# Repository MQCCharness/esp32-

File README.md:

# ESP32-S3 MOC 2.0 开发板资料库

HELLO STEM/嘉年创奇 **ESP32-S3 MOC 2.0** 开发板（生产商：惠州市百育科技有限公司，执行标准 Q/BYKJ 001-2023）的逆向调研、出厂备份与恢复工具合集。

## 板卡档案

| 项目 | 内容 |
|------|------|
| 主控 | ESP32-S3，QFN56，revision v0.2（乐鑫） |
| 内核 | 双核 Xtensa LX7 @ 240 MHz |
| 无线 | Wi-Fi + 蓝牙 5 (LE) |
| 片内 PSRAM | 8 MB（封装内嵌入式，AP 厂商） |
| 板载 Flash | 16 MB，四线 SPI |
| USB | 芯片内置 USB-Serial/JTAG（无外置串口桥），Windows 免驱 |
| 出厂固件 | Arduino 框架测试程序（esp-idf v4.4.4，2023-02-08 编译） |
| 出厂分区 | Arduino OTA 布局：app0/app1 各 1.25MB + SPIFFS 1.375MB |

实测芯片 MAC：`14:c1:9f:46:78:4c`

## 目录说明

```
├── factory_backup/          出厂 Flash 完整备份（4MB 镜像 + 校验与档案说明）
├── one_click_restore/       一键恢复包（免安装，拷到 U 盘即可在任意 Windows 电脑使用）
│   ├── 一键恢复.bat          双击即可恢复出厂（自动识别 COM 口）
│   ├── esptool.exe          乐鑫官方烧录工具独立版 v5.3.1
│   ├── factory_full_4M.bin  出厂固件镜像
│   └── 使用说明.txt
├── caixukun_ascii/          串口 ASCII 动画项目（MicroPython，视频转字符画循环播放）
│   ├── main.py              板端播放器（开机自动播放，REPL Ctrl-C 打断）
│   ├── viewer.py            电脑端串口播放器（自动找 COM 口）
│   ├── 启动动画.bat          双击看动画
│   └── convert_to_ascii.py  视频 → ASCII 帧包转换器（本地使用）
├── third_party/esp32-edu/   韩国教育机构配套课程（git subtree 合并，含板子标注实拍图）
└── docs/                    板卡引脚表、调研结论、踩坑记录与操作规范
```

> **第三方来源声明**：`third_party/esp32-edu` 来自 [parkdongbae-afk/esp32-edu](https://github.com/parkdongbae-afk/esp32-edu)（韩国中学 ESP32-S3-MOC 教学项目，git subtree 合并，版权归原作者；该仓库未见 LICENSE 文件，仅作学习研究用途引用）。

## 快速上手

- **看动画**：双击 `caixukun_ascii/启动动画.bat`（需先 USB 连板）
- **恢复出厂**：双击 `one_click_restore/一键恢复.bat`
- **踩坑速查**：[docs/踩坑记录与操作规范.md](docs/踩坑记录与操作规范.md)（CDC 挂死、UART 重建限制、串口丢包等 7 个坑的根因与 SOP）

## 一键恢复出厂

1. USB 连接开发板
2. 双击 `one_click_restore/一键恢复.bat`
3. 等待约 20 秒，看到「★ 恢复成功」即可

或手动执行：

```bash
esptool.exe --port COMx --baud 921600 write-flash 0x0 factory_full_4M.bin
```

## 引脚速查

详见 [docs/ESP32-S3-MOC-套件引脚表.md](docs/ESP32-S3-MOC-套件引脚表.md)。常用：DHT11→GPIO4，超声波→GPIO5/18，OLED→GPIO8/9，舵机→GPIO14，蜂鸣器→GPIO12，NeoPixel→GPIO13。

**硬约束**：GPIO19/20=USB，GPIO26-32=Flash，GPIO35-37 因 8MB PSRAM 不可用，GPIO0/3/45/46 为 strapping 脚。

## 调研结论（2026-08）

- 该厂商无公开的原理图/引脚图/恢复镜像，公网无索引
- 同型号板卡用于韩国中学编程教育：配套课程软件 [esp32-edu](https://github.com/parkdongbae-afk/esp32-edu)，其数据文件给出了套件标准接线（已整理为上方引脚表）
- ESP32-S3 的 ROM 下载模式无法被软件破坏，**这块板软件层面刷不死**，任何情况下都可用 esptool 重刷

## 备份完整性

`factory_full_4M.bin` SHA256：`ac49514050ef4841609e4c4b86767b0878150f8ae4bd8d039c1a32f8657c1f6b`（4,194,304 字节；4MB 之后至 16MB 为出厂空白 0xFF，已抽样验证）

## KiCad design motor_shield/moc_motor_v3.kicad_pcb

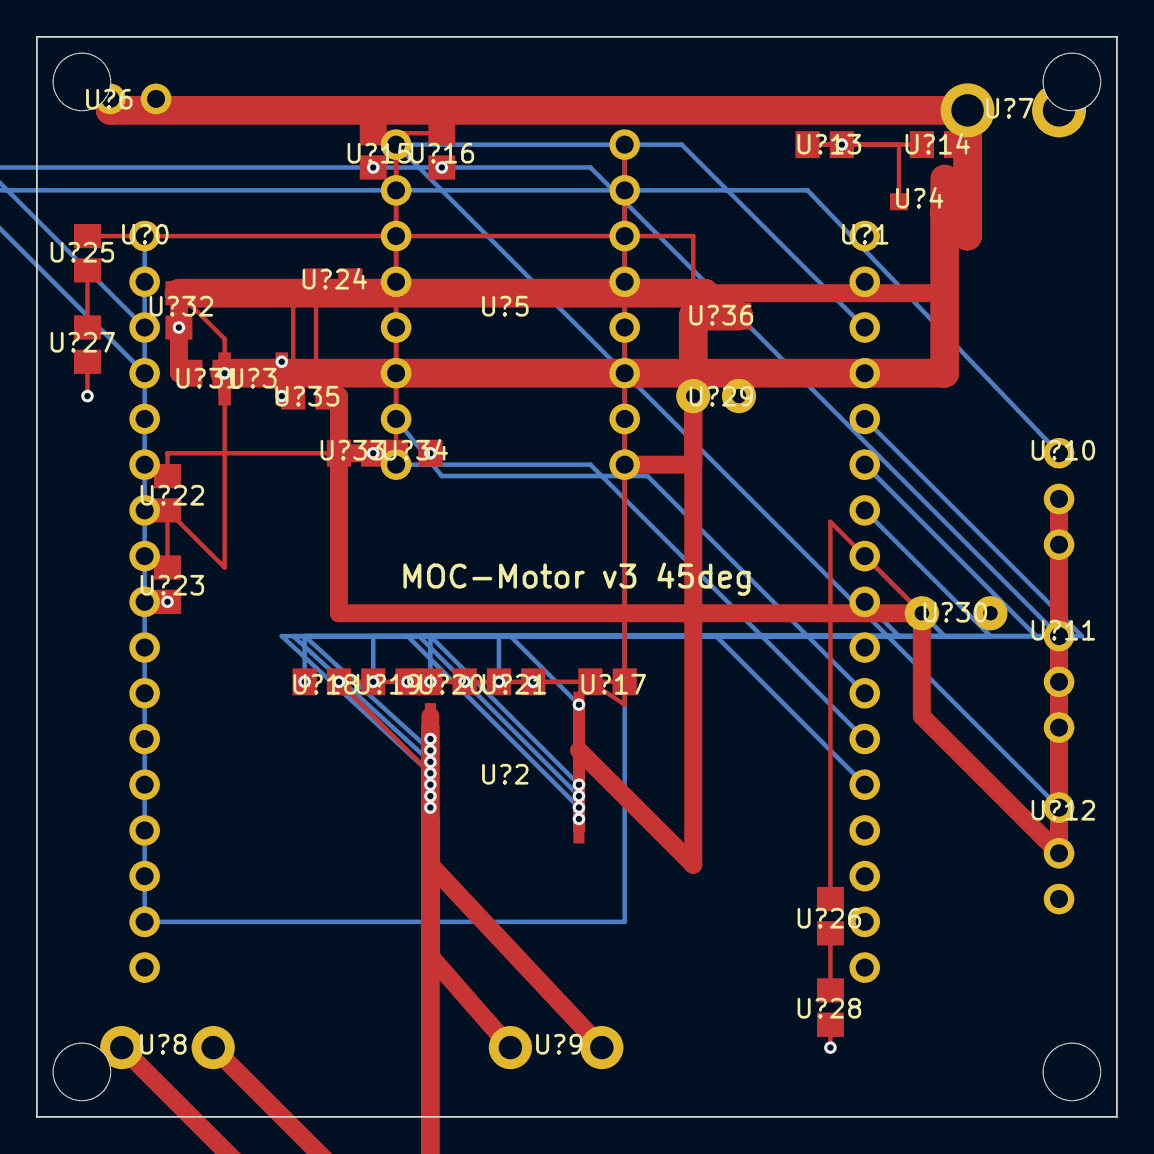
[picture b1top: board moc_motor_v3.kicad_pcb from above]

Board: 2 copper layers, 60.0 x 60.0 mm, 37 parts (0 on the bottom side), 24 nets.

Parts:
U?0: hdr_0
U?1: hdr_1
U?2: sop24_2
U?3: sot23_8_3
U?4: sot23_4
U?5: hdr2x8_5
U?6: hdr_6
U?7: xt30_7
U?8: kf301_8
U?9: kf301_9
U?10: hdr_10
U?11: hdr_11
U?12: hdr_12
U?13: r0805_13
U?14: r0805_14
U?15: r0805_15
U?16: r0805_16
U?17: r0805_17
U?18: r0805_18
U?19: r0805_19
U?20: r0805_20
U?21: r0805_21
U?22: r0805_22
U?23: r0805_23
U?24: r0805_24
U?25: r0805_25
U?26: r0805_26
U?27: r0805_27
U?28: r0805_28
U?29: elco_29
U?30: elco_30
U?31: r0805_31
U?32: r0805_32
U?33: r0805_33
U?34: r0805_34
U?35: r0805_35
U?36: r0805_36

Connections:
+3V3: U?2.3, U?5.9, U?17.1
+5V: U?22.1, U?26.1, U?33.1, U?34.1, U?35.2
+5V_F: U?10.2, U?11.2, U?12.2, U?30.1
AIN1: U?2.5, U?18.1
AIN2: U?2.4, U?19.1
BIN1: U?2.17, U?20.1
BIN2: U?2.16, U?21.1
BST: U?3.7, U?24.1
DIR: U?5.8, U?16.1
FB: U?3.4, U?22.2, U?23.1
GND: U?2.7, U?2.8, U?2.9, U?2.14, U?3.2, U?3.5, U?3.8, U?5.1, U?5.10, U?6.2, U?7.2, U?10.3, U?11.3, U?12.3, U?13.2, U?15.2, U?16.2, U?18.2, U?19.2, U?20.2, U?21.2, U?23.2, U?29.2, U?30.2, U?31.2, U?32.2, U?33.2, U?34.2
LED_5V: U?26.2, U?28.1
LED_VM: U?25.2, U?27.1
MOTA1: U?2.2, U?8.1
MOTA2: U?2.1, U?8.2
MOTB1: U?2.10, U?9.1
MOTB2: U?2.11, U?9.2
STBY: U?2.6, U?17.2
STEP: U?5.7, U?15.1
SW: U?3.6, U?24.2, U?35.1
VGATE: U?4.1, U?13.1, U?14.1
VIN: U?4.3, U?6.1, U?7.1, U?14.2
VIN_F: U?4.2, U?31.1, U?32.1, U?36.1
VM: U?2.19, U?2.20, U?5.16, U?25.1, U?29.1, U?36.2

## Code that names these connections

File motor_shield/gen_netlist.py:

# -*- coding: utf-8 -*-
"""MOC-Motor 扩展板网表生成器
输出:
  1. connections.csv  功能连接表（权威设计依据，人可读）
  2. motor_shield.net KiCad 5 网表（立创EDA/KiCad 可导入）

注意: U1(TB6612FNG)/U3(A4988) 的封装引脚号以数据表为准,
网表中已标注 PROVISIONAL, 导入布局前必须核对。
"""
import csv
import io

# ---------------------------------------------------------------
# 连接表: (网络名, [(器件, 功能脚)])
# 功能脚为逻辑连接关系, 是设计的权威定义
# ---------------------------------------------------------------
NETS = [
    # 电源输入与保护
    ("VIN",        [("J1", "DC005+"), ("J2", "XT30+"), ("Q1", "DRAIN")]),
    ("GND",        [("J1", "DC005-"), ("J2", "XT30-"), ("J5", "GND"),
                    ("U1", "GND"), ("U2", "GND"), ("U3", "GND"),
                    ("J3", "P2"), ("J4", "P2"), ("J6", "P3"), ("J7", "P3"),
                    ("J8", "P3"), ("C1", "P2"), ("C2", "P2"), ("C3", "P2"),
                    ("C4", "P2"), ("C5", "P2"), ("C6", "P2")]),
    ("VM",         [("Q1", "SOURCE"), ("F2", "P1"), ("R10", "P1")]),   # 反接保护后电机轨
    ("VM_FUSED",   [("F2", "P2"), ("U1", "VM"), ("U3", "VM"),
                    ("C1", "P1"), ("U2", "VIN")]),
    ("5V",         [("U2", "VOUT"), ("F1", "P1"), ("C5", "P1"), ("C6", "P1"),
                    ("C2", "P1"), ("R11", "P1")]),
    ("5V_FUSED",   [("F1", "P2"), ("J6", "P2"), ("J7", "P2"), ("J8", "P2")]),
    ("3V3",        [("J5", "3V3"), ("U1", "VCC"), ("U3", "VDD"), ("R5", "P1")]),
    # 反接保护栅极网络
    ("VGATE",      [("Q1", "GATE"), ("R1", "P1"), ("R2", "P1")]),
    ("VIN_S",      [("R2", "P2"), ("C3", "P1")]),           # 栅极采样(接VIN侧) - R2接VIN
    # TB6612 控制 (来自主板排针 J5)
    ("M_AIN1",     [("J5", "GPIO42"), ("U1", "AIN1"), ("R6", "P1")]),
    ("M_AIN2",     [("J5", "GPIO41"), ("U1", "AIN2"), ("R7", "P1")]),
    ("M_PWMA",     [("J5", "GPIO40"), ("U1", "PWMA")]),
    ("M_BIN1",     [("J5", "GPIO39"), ("U1", "BIN1"), ("R8", "P1")]),
    ("M_BIN2",     [("J5", "GPIO38"), ("U1", "BIN2"), ("R9", "P1")]),
    ("M_PWMB",     [("J5", "GPIO21"), ("U1", "PWMB")]),
    ("M_STBY",     [("J5", "GPIO47"), ("U1", "STBY"), ("R5", "P2")]),
    # 电机输出
    ("MOTA+",      [("U1", "AO1"), ("J3", "P1")]),
    ("MOTA-",      [("U1", "AO2"), ("J3", "P1B")]),
    ("MOTB+",      [("U1", "BO1"), ("J4", "P1")]),
    ("MOTB-",      [("U1", "BO2"), ("J4", "P1B")]),
    # 舵机
    ("SRV1_SIG",   [("J5", "GPIO14"), ("J6", "P1")]),
    ("SRV2_SIG",   [("J5", "GPIO15"), ("J7", "P1")]),
    ("SRV3_SIG",   [("J5", "GPIO17"), ("J8", "P1")]),
    # 步进 (A4988 模块插座)
    ("STP_STEP",   [("J5", "GPIO45"), ("U3", "STEP"), ("R3", "P1")]),
    ("STP_DIR",    [("J5", "GPIO46"), ("U3", "DIR"), ("R4", "P1")]),
    # 下拉/上拉电阻落位
    ("GND_PULL",   [("R3", "P2"), ("R4", "P2"), ("R6", "P2"),
                    ("R7", "P2"), ("R8", "P2"), ("R9", "P2")]),
    # 指示灯
    ("LED_VM",     [("R10", "P2"), ("D1", "A")]),
    ("LED_5V",     [("R11", "P2"), ("D2", "A")]),
    ("D1_K",       [("D1", "K")]),
    ("D2_K",       [("D2", "K")]),
]

COMPONENTS = [
    # (位号, 值, 封装, 备注)
    ("U1", "TB6612FNG", "SOP-24", "双路DC驱动 PIN# PROVISIONAL"),
    ("U2", "MP1584EN", "SOT-23-8", "5V/3A降压 含外围"),
    ("U3", "A4988_SOCKET", "PinHeader_2x08", "步进模块插座"),
    ("Q1", "AO3401A", "SOT-23", "反接保护P-MOS"),
    ("F1", "FUSE_3A", "R1206", "5V轨自恢复"),
    ("F2", "FUSE_5A", "R1206", "VM轨自恢复"),
    ("J1", "DC005", "DC005", "电源输入"),
    ("J2", "XT30", "XT30", "电池焊盘"),
    ("J3", "KF301-2P", "KF301-2P", "电机A"),
    ("J4", "KF301-2P", "KF301-2P", "电机B"),
    ("J5", "HDR_2x17", "PinSocket_2x17", "主板对接"),
    ("J6", "SRV_HDR", "PinHeader_1x03", "舵机1"),
    ("J7", "SRV_HDR", "PinHeader_1x03", "舵机2"),
    ("J8", "SRV_HDR", "PinHeader_1x03", "舵机3"),
    ("R1", "100K", "R0805", "Q1栅下拉"),
    ("R2", "10K", "R0805", "Q1栅串联"),
    ("R3", "10K", "R0805", "STEP下拉"),
    ("R4", "10K", "R0805", "DIR下拉"),
    ("R5", "100K", "R0805", "STBY上拉"),
    ("R6", "100K", "R0805", "AIN1下拉"),
    ("R7", "100K", "R0805", "AIN2下拉"),
    ("R8", "100K", "R0805", "BIN1下拉"),
    ("R9", "100K", "R0805", "BIN2下拉"),
    ("R10", "1K", "R0805", "LED_VM限流"),
    ("R11", "1K", "R0805", "LED_5V限流"),
    ("D1", "LED_RED", "LED_0805", "VM指示"),
    ("D2", "LED_GREEN", "LED_0805", "5V指示"),
    ("C1", "100uF_25V", "CP_Tantal", "VM储能"),
    ("C2", "1000uF_16V", "CP_Radial_D8", "舵机浪涌"),
    ("C3", "100nF", "C0805", "U2输入"),
    ("C4", "22uF", "C0805", "U2输入大容量"),
    ("C5", "22uF", "C0805", "U2输出"),
    ("C6", "100nF", "C0805", "U2输出"),
    ("L1", "22uH", "CD54", "MP1584功率电感"),
]

# KiCad 引脚号映射（PROVISIONAL，导入前按数据表核对）
PINNUM = {
    # TB6612FNG SSOP-24（按东芝数据表最终核对）
    "U1": {"AO1": "1", "AO2": "2", "VM": "14", "VCC": "20",
           "GND": "18", "STBY": "19", "AIN1": "21", "AIN2": "22",
           "PWMA": "23", "BIN1": "17", "BIN2": "16", "PWMB": "15",
           "BO1": "11", "BO2": "12"},
    "U3": {"STEP": "7", "DIR": "8", "VM": "16", "VDD": "10",
           "GND": "9", "EN": "1"},
    "Q1": {"GATE": "1", "SOURCE": "2", "DRAIN": "3"},
}

PASSIVE_PINS = 2  # R/C/L/Led 两脚器件 P1/P2 或 A/K


def main():
    # 1) 功能连接表 CSV
    with open("connections.csv", "w", newline="", encoding="utf-8-sig") as f:
        w = csv.writer(f)
        w.writerow(["网络", "器件", "功能脚", "KiCad引脚号(待核对)"])
        for net, nodes in NETS:
            for ref, pin in nodes:
                num = PINNUM.get(ref, {}).get(pin, "")
                w.writerow([net, ref, pin, num])
    print("connections.csv:", sum(len(n) for _, n in NETS), "个连接点")

    # 2) KiCad 网表
    out = io.StringIO()
    out.write("(export (version D)\n")
    out.write("  (design\n    (source \"MOC-Motor Shield v1.0\")\n")
    out.write("    (comment \"PIN NUMBERS OF U1/U3 ARE PROVISIONAL - VERIFY VS DATASHEET\"))\n")
    out.write("  (components\n")
    for ref, val, fp, note in COMPONENTS:
        out.write(f'    (comp (ref {ref})\n')
        out.write(f'      (value "{val}")\n')
        out.write(f'      (footprint "{fp}")\n')
        out.write(f'      (property "Note" "{note}"))\n')
    out.write("  )\n  (nets\n")
    for i, (net, nodes) in enumerate(NETS, 1):
        out.write(f'    (net (code {i}) (name "{net}")\n')
        for ref, pin in nodes:
            if ref in PINNUM and pin in PINNUM[ref]:
                num = PINNUM[ref][pin]
                fmt = f'(pin {num})'
            elif pin in ("A",):
                fmt = "(pin 1)"
            elif pin in ("K",):
                fmt = "(pin 2)"
            elif pin.startswith("P1") or pin == "P1":
                fmt = "(pin 1)"
            elif pin.startswith("P2") or pin == "P2":
                fmt = "(pin 2)"
            else:
                fmt = '(pin "0")'  # 排针功能位 → 布局时映射实际针号
            out.write(f"      (node (ref {ref}) {fmt} (pinfunction {pin}))\n")
        out.write("    )\n")
    out.write("  )\n)\n")
    with open("motor_shield.net", "w", encoding="utf-8") as f:
        f.write(out.getvalue())
    print("motor_shield.net:", len(NETS), "个网络,", len(COMPONENTS), "个器件")


if __name__ == "__main__":
    main()
